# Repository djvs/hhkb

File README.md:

# hhkb

USB/QMK atmega32u4 pcb for HHKB with WS2812B addressable LED support and sonalert buzzer.  

Released without warranty, use at your own risk.  

PRs & feedback welcome!

---

Dimensions: 285 x 100 mm

---

Shield: [![CC BY-SA 4.0][cc-by-sa-shield]][cc-by-sa]

This work is licensed under a
[Creative Commons Attribution-ShareAlike 4.0 International License][cc-by-sa].

[![CC BY-SA 4.0][cc-by-sa-image]][cc-by-sa]

[cc-by-sa]: http://creativecommons.org/licenses/by-sa/4.0/
[cc-by-sa-image]: https://licensebuttons.net/l/by-sa/4.0/88x31.png
[cc-by-sa-shield]: https://img.shields.io/badge/License-CC%20BY--SA%204.0-lightgrey.svg

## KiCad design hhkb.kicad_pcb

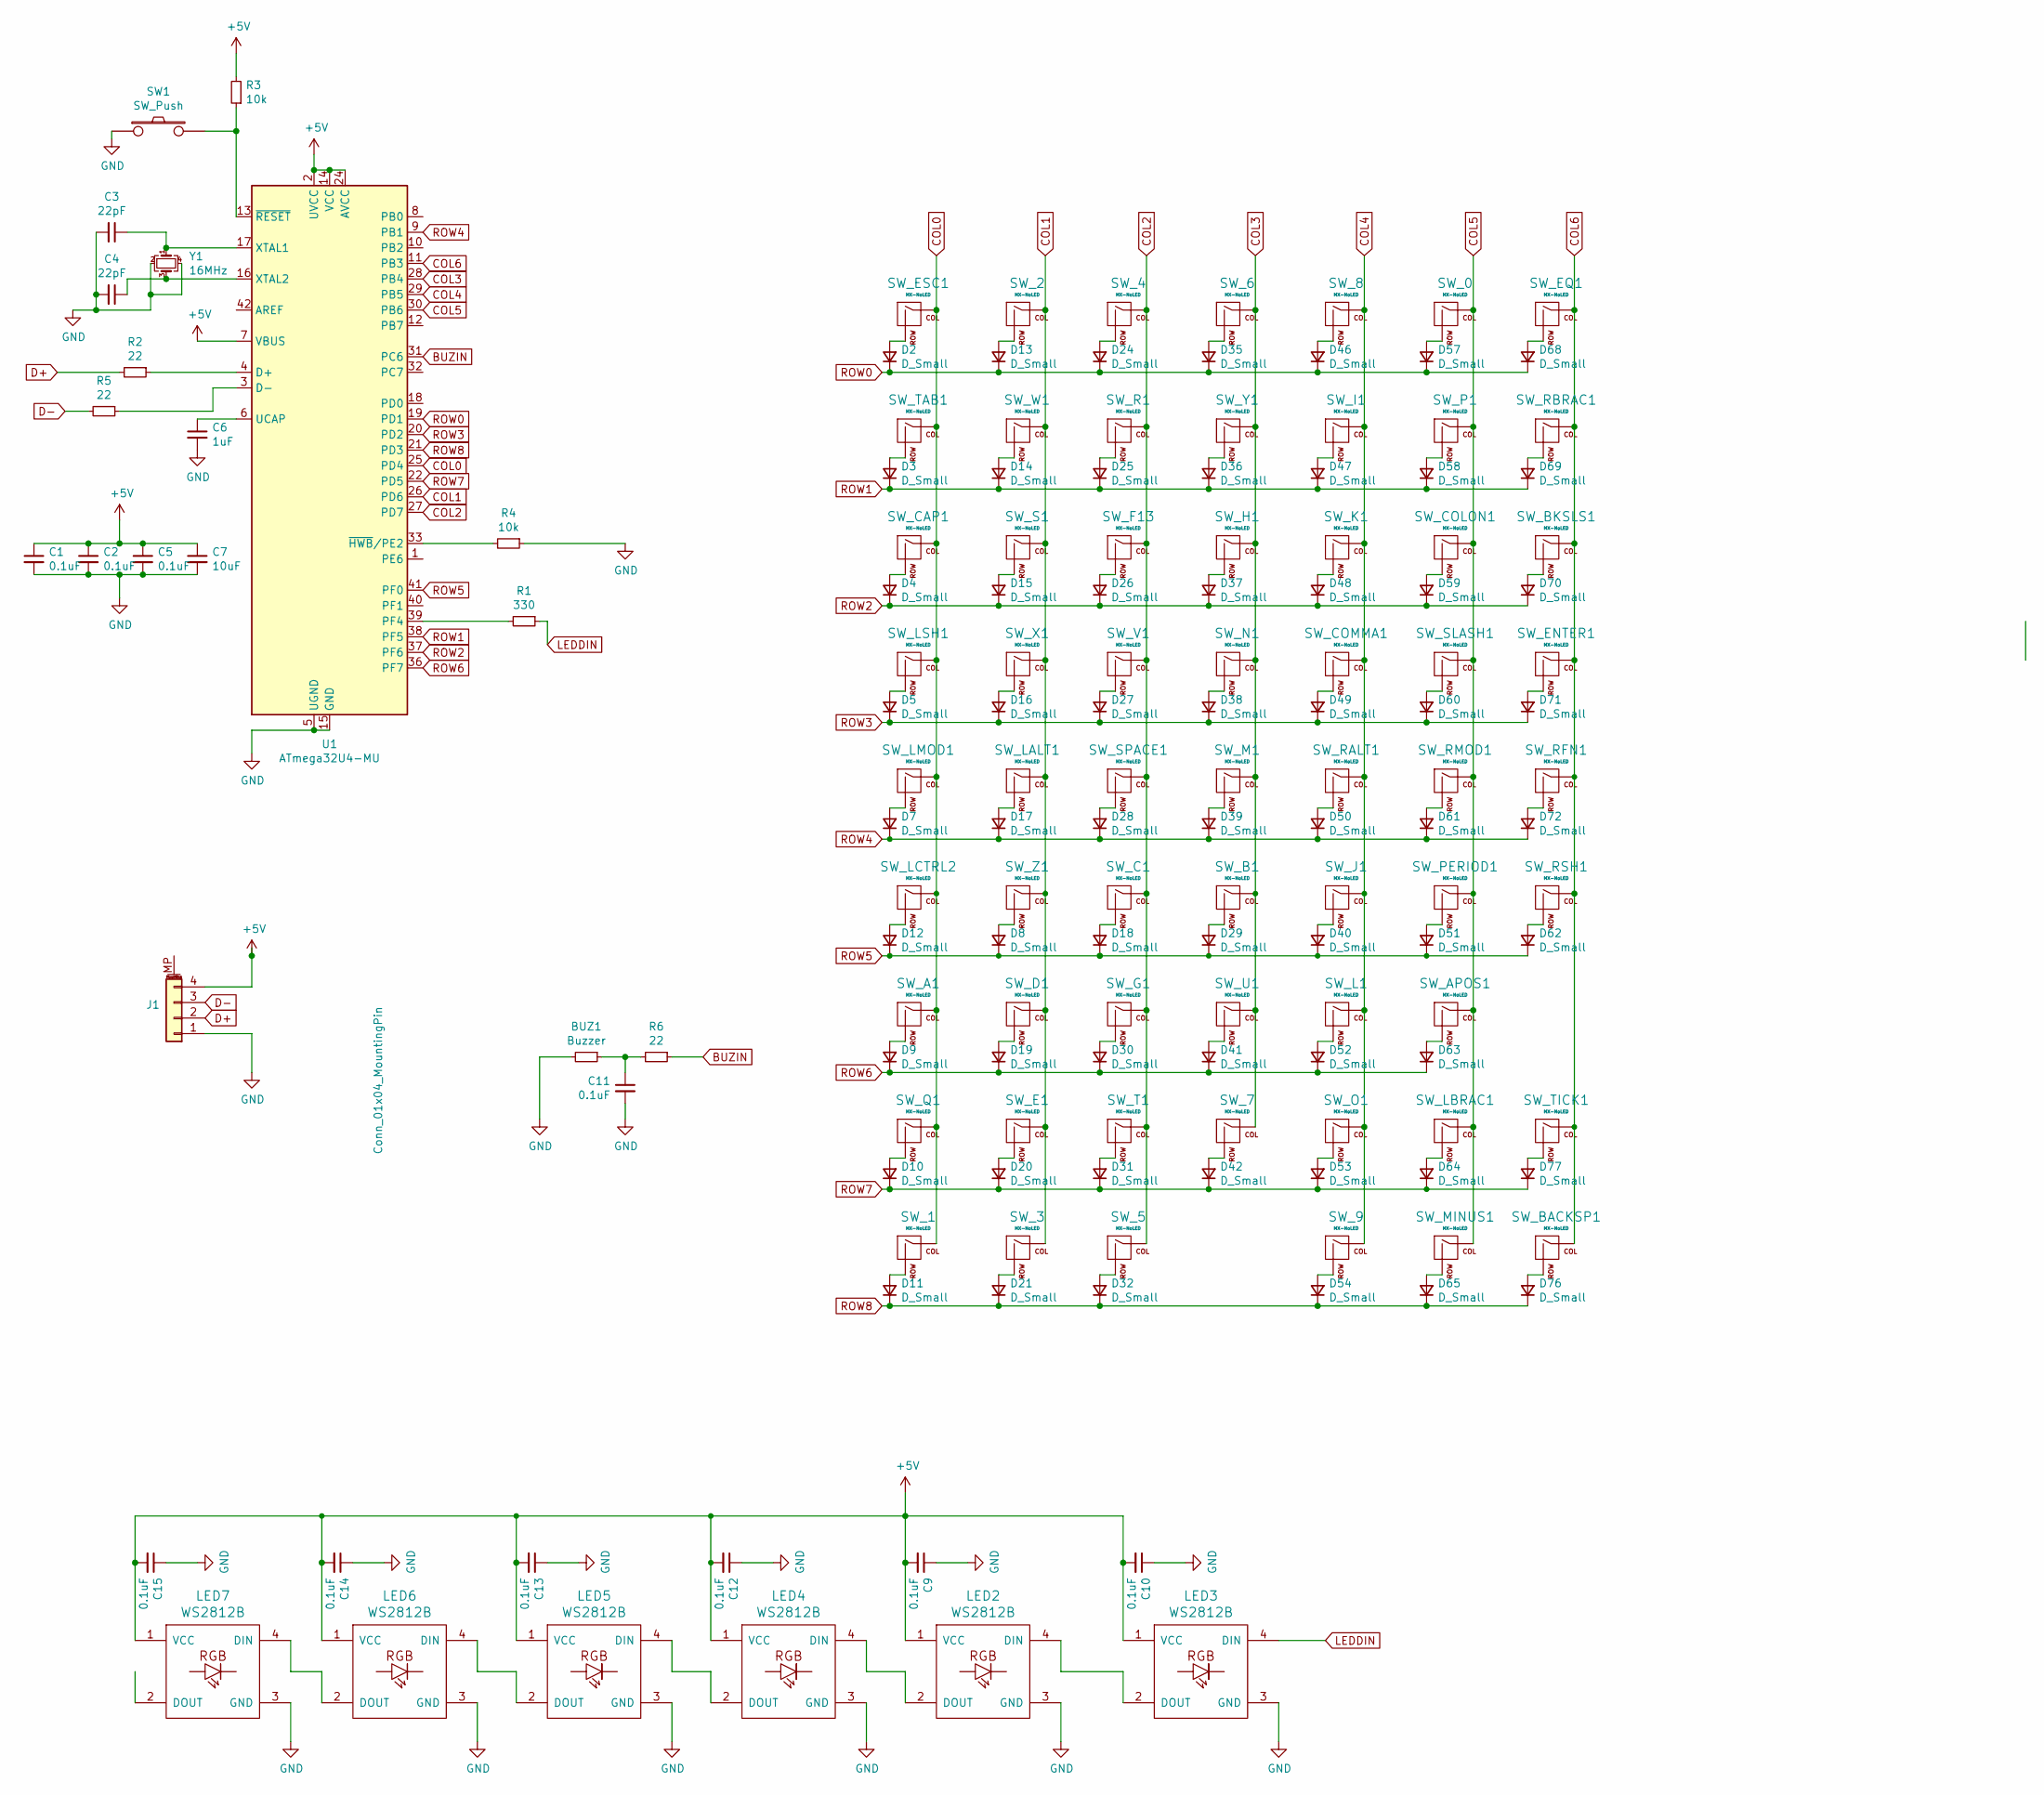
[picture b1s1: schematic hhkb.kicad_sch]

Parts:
BUZ1: Buzzer; Buzzer_Mallory_AST1109MLTRQ
C1, C2, C5, C9, C10, C11, C12, C13, C14, C15: 0.1uF; C_0805_2012Metric
C3, C4: 22pF; C_0805_2012Metric
C6: 1uF; C_0805_2012Metric
C7: 10uF; C_0805_2012Metric
D2, D3, D4, D5, D7, D8, D9, D10, D11, D12, D13, D14, D15, D16, D17, D18, D19, D20, D21, D24, D25, D26, D27, D28, D29, D30, D31, D32, D35, D36, D37, D38, D39, D40, D41, D42, D46, D47, D48, D49, D50, D51, D52, D53, D54, D57, D58, D59, D60, D61, D62, D63, D64, D65, D68, D69, D70, D71, D72, D76, D77: D_Small; D_SOD-123
J1: Conn_01x04_MountingPin; JST_SH_SM04B-SRSS-TB_1x04-1MP_P1.00mm_Horizontal
LED2, LED3, LED4, LED5, LED6, LED7: WS2812B; WS2812BDual
R1: 330; R_0805_2012Metric
R2, R5, R6: 22; R_0805_2012Metric
R3, R4: 10k; R_0805_2012Metric
SW1: SW_Push; SKQG-1155865
SW_0, SW_1, SW_2, SW_3, SW_4, SW_5, SW_6, SW_7, SW_8, SW_9: MX-NoLED; mx-nec-alps
SW_A1: MX-NoLED; mx-nec-alps
SW_APOS1: MX-NoLED; mx-nec-alps
SW_B1: MX-NoLED; mx-nec-alps
SW_BACKSP1: MX-NoLED; mx-nec-alps
SW_BKSLS1: MX-NoLED; mx-nec-alps
SW_C1: MX-NoLED; mx-nec-alps
SW_CAP1: MX-NoLED; mx-nec-alps
SW_COLON1: MX-NoLED; mx-nec-alps
SW_COMMA1: MX-NoLED; mx-nec-alps
SW_D1: MX-NoLED; mx-nec-alps
SW_E1: MX-NoLED; mx-nec-alps
SW_ENTER1: MX-NoLED; mx-nec-alps
SW_EQ1: MX-NoLED; mx-nec-alps
SW_ESC1: MX-NoLED; mx-nec-alps
SW_F13: MX-NoLED; mx-nec-alps
SW_G1: MX-NoLED; mx-nec-alps
SW_H1: MX-NoLED; mx-nec-alps
SW_I1: MX-NoLED; mx-nec-alps
SW_J1: MX-NoLED; mx-nec-alps
SW_K1: MX-NoLED; mx-nec-alps
SW_L1: MX-NoLED; mx-nec-alps
SW_LALT1: MX-NoLED; mx-nec-alps
SW_LBRAC1: MX-NoLED; mx-nec-alps
SW_LCTRL2: MX-NoLED; mx-nec-alps
SW_LMOD1: MX-NoLED; mx-nec-alps
SW_LSH1: MX-NoLED; mx-nec-alps
SW_M1: MX-NoLED; mx-nec-alps
SW_MINUS1: MX-NoLED; mx-nec-alps
SW_N1: MX-NoLED; mx-nec-alps
SW_O1: MX-NoLED; mx-nec-alps
SW_P1: MX-NoLED; mx-nec-alps
SW_PERIOD1: MX-NoLED; mx-nec-alps
SW_Q1: MX-NoLED; mx-nec-alps
SW_R1: MX-NoLED; mx-nec-alps
SW_RALT1: MX-NoLED; mx-nec-alps
SW_RBRAC1: MX-NoLED; mx-nec-alps
SW_RFN1: MX-NoLED; mx-nec-alps
SW_RMOD1: MX-NoLED; mx-nec-alps
SW_RSH1: MX-NoLED; mx-nec-alps
SW_S1: MX-NoLED; mx-nec-alps
SW_SLASH1: MX-NoLED; mx-nec-alps
SW_SPACE1: MX-NoLED; MX-6.5U-ReversedStabilizers-NoLED
SW_T1: MX-NoLED; mx-nec-alps
SW_TAB1: MX-NoLED; mx-nec-alps
SW_TICK1: MX-NoLED; mx-nec-alps
SW_U1: MX-NoLED; mx-nec-alps
SW_V1: MX-NoLED; mx-nec-alps
SW_W1: MX-NoLED; mx-nec-alps
SW_X1: MX-NoLED; mx-nec-alps
SW_Y1: MX-NoLED; mx-nec-alps
SW_Z1: MX-NoLED; mx-nec-alps
U1: ATmega32U4-MU; atmega32u4-mu-and-au
Y1: 16MHz; Crystal_SMD_3225-4Pin_3.2x2.5mm

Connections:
+5V: C1.1, C2.1, C5.1, C7.1, C9.2, C10.2, C12.2, C13.2, C14.2, C15.2, J1.4, LED2.1 (VCC), LED3.1 (VCC), LED4.1 (VCC), LED5.1 (VCC), LED6.1 (VCC), LED7.1 (VCC), R3.2, U1.2 (UVCC), U1.7 (VBUS), U1.14 (VCC), U1.24 (AVCC), U1.34 (VCC), U1.44 (AVCC)
BUZIN: R6.1, U1.31 (PC6)
COL0: SW_1.1 (COL), SW_A1.1 (COL), SW_CAP1.1 (COL), SW_ESC1.1 (COL), SW_LCTRL2.1 (COL), SW_LMOD1.1 (COL), SW_LSH1.1 (COL), SW_Q1.1 (COL), SW_TAB1.1 (COL), U1.25 (PD4)
COL1: SW_2.1 (COL), SW_3.1 (COL), SW_D1.1 (COL), SW_E1.1 (COL), SW_LALT1.1 (COL), SW_S1.1 (COL), SW_W1.1 (COL), SW_X1.1 (COL), SW_Z1.1 (COL), U1.26 (PD6)
COL2: SW_4.1 (COL), SW_5.1 (COL), SW_C1.1 (COL), SW_F13.1 (COL), SW_G1.1 (COL), SW_R1.1 (COL), SW_SPACE1.1 (COL), SW_T1.1 (COL), SW_V1.1 (COL), U1.27 (PD7)
COL3: SW_6.1 (COL), SW_7.1 (COL), SW_B1.1 (COL), SW_H1.1 (COL), SW_M1.1 (COL), SW_N1.1 (COL), SW_U1.1 (COL), SW_Y1.1 (COL), U1.28 (PB4)
COL4: SW_8.1 (COL), SW_9.1 (COL), SW_COMMA1.1 (COL), SW_I1.1 (COL), SW_J1.1 (COL), SW_K1.1 (COL), SW_L1.1 (COL), SW_O1.1 (COL), SW_RALT1.1 (COL), U1.29 (PB5)
COL5: SW_0.1 (COL), SW_APOS1.1 (COL), SW_COLON1.1 (COL), SW_LBRAC1.1 (COL), SW_MINUS1.1 (COL), SW_P1.1 (COL), SW_PERIOD1.1 (COL), SW_RMOD1.1 (COL), SW_SLASH1.1 (COL), U1.30 (PB6)
COL6: SW_BACKSP1.1 (COL), SW_BKSLS1.1 (COL), SW_ENTER1.1 (COL), SW_EQ1.1 (COL), SW_RBRAC1.1 (COL), SW_RFN1.1 (COL), SW_RSH1.1 (COL), SW_TICK1.1 (COL), U1.11 (PB3)
D+: J1.2, R2.2
D-: J1.3, R5.2
GND: BUZ1.2, C1.2, C2.2, C3.2, C4.2, C5.2, C6.2, C7.2, C9.1, C10.1, C11.2, C12.1, C13.1, C14.1, C15.1, J1.1, LED2.3 (GND), LED3.3 (GND), LED4.3 (GND), LED5.3 (GND), LED6.3 (GND), LED7.3 (GND), R4.1, SW1.1, U1.5 (UGND), U1.15 (GND), U1.23 (GND), U1.35 (GND), U1.43 (GND), U1.45 (GND), Y1.2, Y1.4
LEDDIN: LED3.4 (DIN), R1.1
unnamed: BUZ1.1, C11.1, R6.2
unnamed: D2.2 (A), SW_ESC1.2 (ROW)
unnamed: D3.2 (A), SW_TAB1.2 (ROW)
unnamed: D4.2 (A), SW_CAP1.2 (ROW)
unnamed: D5.2 (A), SW_LSH1.2 (ROW)
unnamed: D7.2 (A), SW_LMOD1.2 (ROW)
unnamed: D8.2 (A), SW_Z1.2 (ROW)
unnamed: D9.2 (A), SW_A1.2 (ROW)
unnamed: D10.2 (A), SW_Q1.2 (ROW)
unnamed: D11.2 (A), SW_1.2 (ROW)
unnamed: D12.2 (A), SW_LCTRL2.2 (ROW)
unnamed: D13.2 (A), SW_2.2 (ROW)
unnamed: D14.2 (A), SW_W1.2 (ROW)
unnamed: D15.2 (A), SW_S1.2 (ROW)
unnamed: D16.2 (A), SW_X1.2 (ROW)
unnamed: D17.2 (A), SW_LALT1.2 (ROW)
unnamed: D18.2 (A), SW_C1.2 (ROW)
unnamed: D19.2 (A), SW_D1.2 (ROW)
unnamed: D20.2 (A), SW_E1.2 (ROW)
unnamed: D21.2 (A), SW_3.2 (ROW)
unnamed: D24.2 (A), SW_4.2 (ROW)
unnamed: D25.2 (A), SW_R1.2 (ROW)
unnamed: D26.2 (A), SW_F13.2 (ROW)
unnamed: D27.2 (A), SW_V1.2 (ROW)
unnamed: D28.2 (A), SW_SPACE1.2 (ROW)
unnamed: D29.2 (A), SW_B1.2 (ROW)
unnamed: D30.2 (A), SW_G1.2 (ROW)
unnamed: D31.2 (A), SW_T1.2 (ROW)
unnamed: D32.2 (A), SW_5.2 (ROW)
unnamed: D35.2 (A), SW_6.2 (ROW)
unnamed: D36.2 (A), SW_Y1.2 (ROW)
unnamed: D37.2 (A), SW_H1.2 (ROW)
unnamed: D38.2 (A), SW_N1.2 (ROW)
unnamed: D39.2 (A), SW_M1.2 (ROW)
unnamed: D40.2 (A), SW_J1.2 (ROW)
unnamed: D41.2 (A), SW_U1.2 (ROW)
unnamed: D42.2 (A), SW_7.2 (ROW)
unnamed: D46.2 (A), SW_8.2 (ROW)
unnamed: D47.2 (A), SW_I1.2 (ROW)
unnamed: D48.2 (A), SW_K1.2 (ROW)
unnamed: D49.2 (A), SW_COMMA1.2 (ROW)
unnamed: D50.2 (A), SW_RALT1.2 (ROW)
unnamed: D51.2 (A), SW_PERIOD1.2 (ROW)
unnamed: D52.2 (A), SW_L1.2 (ROW)
unnamed: D53.2 (A), SW_O1.2 (ROW)
unnamed: D54.2 (A), SW_9.2 (ROW)
unnamed: D57.2 (A), SW_0.2 (ROW)
unnamed: D58.2 (A), SW_P1.2 (ROW)
unnamed: D59.2 (A), SW_COLON1.2 (ROW)
unnamed: D60.2 (A), SW_SLASH1.2 (ROW)
unnamed: D61.2 (A), SW_RMOD1.2 (ROW)
unnamed: D62.2 (A), SW_RSH1.2 (ROW)
unnamed: D63.2 (A), SW_APOS1.2 (ROW)
unnamed: D64.2 (A), SW_LBRAC1.2 (ROW)
unnamed: D65.2 (A), SW_MINUS1.2 (ROW)
unnamed: D68.2 (A), SW_EQ1.2 (ROW)
unnamed: D69.2 (A), SW_RBRAC1.2 (ROW)
unnamed: D70.2 (A), SW_BKSLS1.2 (ROW)
unnamed: D71.2 (A), SW_ENTER1.2 (ROW)
unnamed: D72.2 (A), SW_RFN1.2 (ROW)
unnamed: D76.2 (A), SW_BACKSP1.2 (ROW)
unnamed: D77.2 (A), SW_TICK1.2 (ROW)
unnamed: LED2.4 (DIN), LED3.2 (DOUT)
unnamed: LED2.2 (DOUT), LED4.4 (DIN)
unnamed: LED4.2 (DOUT), LED5.4 (DIN)
unnamed: LED5.2 (DOUT), LED6.4 (DIN)
unnamed: LED6.2 (DOUT), LED7.4 (DIN)
unnamed: R2.1, U1.4 (D+)
unnamed: R5.1, U1.3 (D-)
unnamed: R1.2, U1.39 (PF4)
unnamed: C6.1, U1.6 (UCAP)
unnamed: C3.1, U1.17 (XTAL1), Y1.1
unnamed: C4.1, U1.16 (XTAL2), Y1.3
unnamed: R4.2, U1.33 (~HWB/PE2)
unnamed: R3.1, SW1.2, U1.13 (~RESET)
ROW0: D2.1 (K), D13.1 (K), D24.1 (K), D35.1 (K), D46.1 (K), D57.1 (K), D68.1 (K), U1.19 (PD1)
ROW1: D3.1 (K), D14.1 (K), D25.1 (K), D36.1 (K), D47.1 (K), D58.1 (K), D69.1 (K), U1.38 (PF5)
ROW2: D4.1 (K), D15.1 (K), D26.1 (K), D37.1 (K), D48.1 (K), D59.1 (K), D70.1 (K), U1.37 (PF6)
ROW3: D5.1 (K), D16.1 (K), D27.1 (K), D38.1 (K), D49.1 (K), D60.1 (K), D71.1 (K), U1.20 (PD2)
ROW4: D7.1 (K), D17.1 (K), D28.1 (K), D39.1 (K), D50.1 (K), D61.1 (K), D72.1 (K), U1.9 (PB1)
ROW5: D8.1 (K), D12.1 (K), D18.1 (K), D29.1 (K), D40.1 (K), D51.1 (K), D62.1 (K), U1.41 (PF0)
ROW6: D9.1 (K), D19.1 (K), D30.1 (K), D41.1 (K), D52.1 (K), D63.1 (K), U1.36 (PF7)
ROW7: D10.1 (K), D20.1 (K), D31.1 (K), D42.1 (K), D53.1 (K), D64.1 (K), D77.1 (K), U1.22 (PD5)
ROW8: D11.1 (K), D21.1 (K), D32.1 (K), D54.1 (K), D65.1 (K), D76.1 (K), U1.21 (PD3)

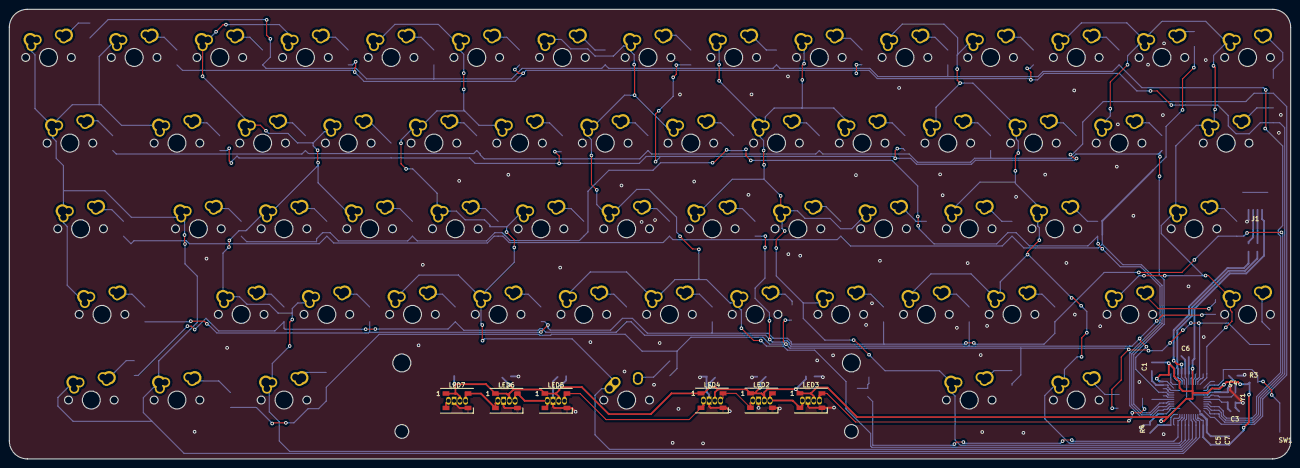
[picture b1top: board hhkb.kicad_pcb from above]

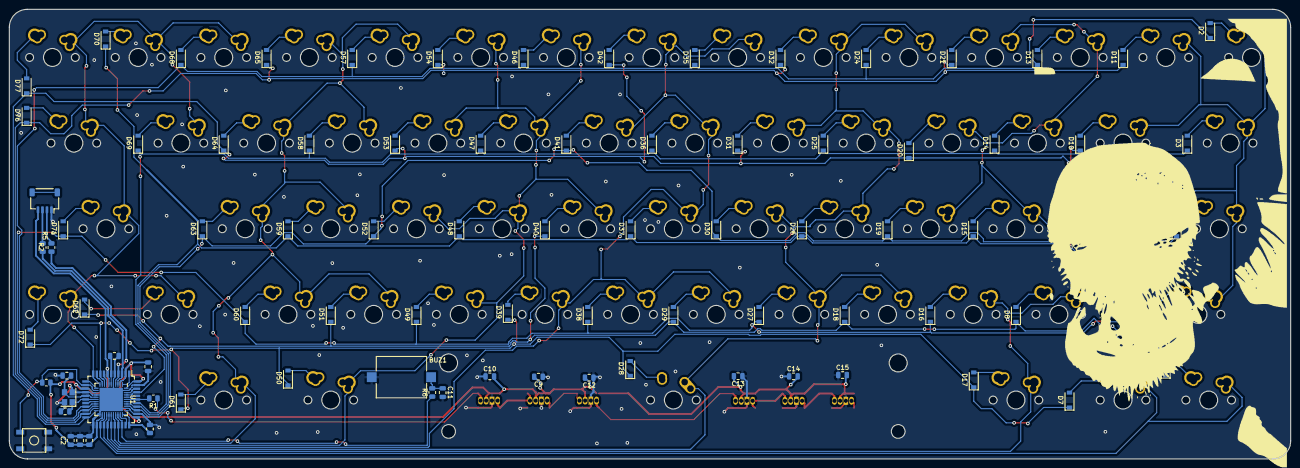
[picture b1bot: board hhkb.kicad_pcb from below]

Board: 2 copper layers, 285.0 x 100.0 mm, 153 parts (86 on the bottom side), 97 nets.

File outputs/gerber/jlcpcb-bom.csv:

Comment,Footprint,Designator,JLCPCB Part #（optional )
"D_Small","D_SOD-123","D12,D16,D2,D3,D4,D5,D7,D8,D9,D10,D11,D13,D14,D15,D17,D18,D19,D20,D21,D24,D25,D26,D27,D28,D29,D30,D31,D32,D35,D36,D37,D38,D39,D40,D41,D42,D46,D47,D48,D49,D50,D51,D52,D53,D54,D57,D58,D59,D60,D61,D62,D63,D64,D65,D68,D69,D70,D71,D72,D76,D77","C81598"
"0.1uF","C_0805_2012Metric","C9,C1,C2,C5,C10,C12,C11,C14,C15,C13","C49678"
"330","R_0805_2012Metric","R1","C17630"
"SW_Push","SKQG-1155865","SW1","C318884"
"1uF","C_0805_2012Metric","C6","C28323"
"10uF","C_0805_2012Metric","C7","C15850"
"Conn_01x04_MountingPin","JST_SH_SM04B-SRSS-TB_1x04-1MP_P1.00mm_Horizontal","J1","C160404"
"10k","R_0805_2012Metric","R3,R4","C17414"
"ATmega32U4-MU","atmega32u4-mu-and-au","U1","C44854"
"16MHz","Crystal_SMD_3225-4Pin_3.2x2.5mm","Y1","C13738"
"22pF","C_0805_2012Metric","C3,C4","C1804"
"22","R_0805_2012Metric","R5,R2,R6","C17561"

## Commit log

2023-01-13 fix kle json
